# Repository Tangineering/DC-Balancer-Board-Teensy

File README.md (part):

# Scale_Car_Teensy

Teensy 4.1 firmware for a scale FCHEV (Fuel-Cell Hybrid EV) platform — the **Scale Car DC
Balancer Board, Rev 20260622**.

The board is a bidirectional power-pathing balancer: ideal-diode source switches route a fuel
cell and a 2S battery onto a shared VBUS, a regen path returns braking energy to the charger,
and an MPPT module harvests into the battery. This firmware drives that hardware.

It controls:
- motor torque through a VESC (`VescUart` over UART),
- fuel-cell/battery power sharing through dual AD5443 MDAC droop outputs (SPI),
- the RT1987 ideal-diode power-path switches (6 sequenced GPIOs),
- the Silvertel **Ag105** MPPT battery charger (I2C config + `MPPT_DISABLE` GPIO),
- the BQ29200 cell OVP/balancer (`CBAL_DISABLE` GPIO),
- command/telemetry with a Raspberry Pi over UDP Ethernet,
- a safety state machine, Pi watchdog, latching fault handling, and a USB-serial test mode.

> The authoritative hardware sources are `references/Scale Car Teensy IO - IO.csv` (pin map),
> `references/Scale Car Design PCB BOM 20260622.csv` (parts), and the schematic PDF. See
> `CLAUDE.md` for the reconciliation spec and `PLAN.md` for the implementation plan. For
> hardware-in-the-loop testing (a bare Teensy against a simulated plant, no PCB needed), see
> `docs/HIL_MODE.md` (protocol/architecture) and `docs/HIL_USER_MANUAL.md` (operator manual).

## Hardware interfaces

- **UART (`Serial1`)**: VESC motor controller (`RX`=0, `TX`=1).
- **SPI**: two AD5443 MDACs (`CS_MDAC_FC`=36, `CS_MDAC_BT`=37) for FC/BT droop gains; OPA197
  output buffers run from the 5 V rail (hardware bodge).
- **I2C (`Wire`)**: Silvertel **Ag105** charger at address **0x30**.
- **Ethernet/UDP**: command in (port 5001), telemetry out (port 5000), Teensy IP 192.168.1.50.
- **Encoder interrupts**: wheel-speed estimation from `ENC_A`=14 / `ENC_B`=15 (bodged from 2/8 on
  2026-08-16; the optical sensors are hardwired to power, so there is no enable pin).
- **ADC inputs (12-bit)**: FC/BT current (INA253A1, 0.1 V/A), FC/BT/BUS/CHG/RGN voltages.
- **Digital outputs**: FC/BT boost enables, 6 RT1987 path switches, `MPPT_DISABLE`,
  `CBAL_DISABLE`, encoder enable.

### Power-path switches (RT1987 ideal-diode controllers)

| Pin | Name | Role |
|----|------|------|
| 27 | `FC_BUS_ENABLE` | FC regulator → VBUS |
| 28 | `BT_BUS_ENABLE` | BT regulator → VBUS |
| 29 | `MOT_PWR_ENABLE` | VBUS → VESC/motor (Run only) |
| 30 | `REGEN_ENABLE` | regen → charger input |
| 31 | `FC_CHARGE_ENABLE` | VBUS(FC) → charger (guarded) |
| 32 | `BT_SEQUENCE_ENABLE` | battery-pack sequencing (init LOW, then HIGH) |

All switches default LOW at boot (fail-safe; 10 kΩ EN-to-GND bodge resistors back this up).
`FC_CHARGE_ENABLE` and `REGEN_ENABLE` are **mutually exclusive** and are only ever driven
through `assertFcChargeEnable()`, which forces `BT_BUS_ENABLE` and `REGEN_ENABLE` LOW (with an
RT1987 turn-off settle delay) before opening the FC→charger path.

**VBUS bring-up — only enable a boost on a stiff source.** The hazard is *not* bus inrush: VBUS
carries only ~30–40 µF (the RT1987 ceramics); the 470 µF bulk cap is on the V-MOT/regen node behind
`MOT_PWR_ENABLE`. The real failure mode is enabling a boost on a source that can **collapse**:
switching with built-up inductor current on a sagging/recovering rail destroys the power stage. The
exact mechanism is **unconfirmed pending a scope capture** — most likely a VOUT overshoot past the
20 V SW/VOUT abs-max (the TPS61288 OVP is at 19 V, only ~0.5 V of margin, and the 3×22 µF output
caps DC-derate to ~30 µF) and/or transient reverse conduction. Either way the destructive energy
comes from the boost's own inductor/output cap, so *a supply current limit does not bound it*. On a
board-powered Teensy this also motorboats: the boost loads `VBT`, the logic rail browns out, the MCU
resets, and re-enables the boost. So in **production** (`BENCH_TEST=0`, stiff vehicle source) State 0
brings the bus up gently (switches first, then the boosts' own soft-start) and is mirrored by the
State 98 `G` command; the bus is then kept energized through Idle/Finish so a Run never re-hot-plugs
it. Under **`BENCH_TEST`** State 0 keeps the power stage **off** at boot (see State 0 below). Bench
rule: the supply must exceed the logic baseline (≥ ~0.5–1 A) or the board-powered Teensy browns out,
and the bus may be brought up (`G`) only on a stiff supply.

## Runtime flow

Main loop execution order:
1. `updateSensors()`
2. `computeDerivedSignals()`
3. `detectFaults()`
4. `checkPiWatchdog()`
5. `receiveCommands()`
6. state machine (`doState0/1/2/3/98/99`)
7. `pollAg105()` + `sendTelemetry()` at ~50 Hz

## State machine

- **State 0 (Init)**: behavior depends on the `BENCH_TEST` build flag.
  - **Production (`BENCH_TEST=0`)**: a **non-blocking phase machine** that brings VBUS up gently —
    bus switches first (`FC_BUS_ENABLE`/`BT_BUS_ENABLE`), settle, then the FC/BT boosts (their
    soft-start raises the bus; see *VBUS bring-up* above). Raises `BT_SEQUENCE_ENABLE`, inits the
    MDAC and VESC, then **gates the transition to Idle on `V_bus ≥ V_BUS_CHARGED_THRESH`**; if the
    bus never reaches it within `BUS_CHARGE_TIMEOUT_MS`, raises `FAULT_INIT_FAIL` → State 99
    (catches a dead boost, failed switch, or no source).
  - **Bench (`BENCH_TEST=1`, the default flash)**: boots **straight to Idle with the power stage
    OFF** — boosts, bus switches, and `BT_SEQUENCE` all stay LOW, and there is no `V_bus` gate. This
    prevents enabling a boost on a soft/current-limited bench supply (which browns out the
    board-powered Teensy and motorboats the boost to failure). Bring the bus up manually with the
    State 98 `G` command on a stiff supply.
  - Either way the Ag105 is **not** configured here — it is unpowered in Init; `pollAg105()`
    configures it lazily once a charger path powers it. Shared init lives in `initControlPeripherals()`.
- **State 1 (Idle)**: motor current zero, `MOT_PWR_ENABLE` LOW; the bus is left **energized**
  (boosts + bus switches stay ON). Waits for a Run command from the Pi, or `T` on USB serial to
  enter test mode (State 98).
- **State 2 (Run)**: `MOT_PWR_ENABLE` HIGH; run `chargingControl()`, `motorControl()`,
  `powerBalance()`. `chargingControl()` owns the `REGEN`/`FC_CHARGE`/`BT_BUS` switches and the
  `MPPT_DISABLE` line. The bus is already up from Init/Idle, so entering Run does not hot-plug it.
- **State 3 (Finish)**: stops the motor and closes the motor/regen/charge paths, but **leaves the
  boosts + bus switches ON** so the bus stays armed and the next Idle→Run never re-hot-plugs the
  470 µF bus. Clears the wheel-speed buffer and returns to Idle. (No cap/regen drain — the
  disabled-boost back-feed hazard doesn't apply while the boosts stay enabled.)
- **State 98 (Test)**: USB-serial hardware exerciser (see below).
- **State 99 (Error)**: **non-blocking** two-phase safe shutdown that bleeds VBUS/regen energy and
  then disables the boosts and tears the bus down — latched until power cycle (which re-runs the
  State-0 gentle bring-up).

The State 99 shutdown is a phase machine gated on `millis()` (no blocking `delay()`), so
`detectFaults()` keeps sampling through the highest-energy drain windows.

## Charger control (Silvertel Ag105)

There is **no charge-current register to program per-mA**. Control is:
- **I2C config is LAZY, not at init** (`pollAg105()`): the charger is unpowered in
  Init/Idle (no charger power path is open, so it cannot ACK I2C), so reg `0x00 = 0x01`
  (2.5 A profile) and reg `0x01 = 0x08` (2S / 8.4 V) are written the first time
  `chargerHasPower()` is true and the `AG105_SETTLE_MS` bring-up window has elapsed and
  the charger ACKs. Stored in EPROM; the flag re-arms on power loss, so writes are
  idempotent. **fw v24** adds a dynamic reg `0x02` MPPT input-voltage threshold, written
  through the same power-gated lazy path with a read-verify-write handshake and an
  EPROM-wear write-rate budget.
- **`MPPT_DISABLE` GPIO (pin 5, active-LOW)**: LOW inhibits the MPPT loop (during regen,
  so it doesn't fight the fast transient); HIGH releases it (cruise/coast harvest). The
  Ag105's MPPT mechanism is an **input-voltage-threshold regulator** (datasheet p.10),
  not perturb-and-observe — charging commences only once the input exceeds a threshold
  set by reg `0x02` (11–33 V, ~0.088 V/count; default 18 V with no MPPTS resistor
  fitted).
- **I2C polling** (`pollAg105()` at 50 Hz): reads reg `0x06` (measured charge current,
  0.011 A/count) into `I_charge`, and caches the Table-6 status byte. The Ag105 prepends its
  status byte before any read, so each 1-byte field is read as 2 bytes.
- **Readiness** (`ag105IsReady()`): GENSTAT (status bits [2:0]) == Charging (0x02) or
  Fully Charged (0x03).
- An Ag105 I2C read failure only latches State 99 in the charging-relevant states (Run/Finish);
  in Init/Idle/Test a missing or still-powering charger does not lock the system.

## Telemetry & commands

- **Commands**: 22-byte UDP packet (sync `0xBB` + XOR checksum). Fields: timestamp, counter,
  `v_setpoint`, `power_share_setpoint`, `charge_goal`, `mode_cmd`, and a reserved `droop_enable`
  byte (parsed, not yet wired).
- **Telemetry — protocol v4, 58 bytes** (`TELEMETRY_VERSION = 4`, sync `0xAA`, XOR over bytes
  1–56). Carries the measured/derived signals, droop gains, the raw Ag105 Table-6
  `charger_status` byte (offset 51), a `switch_state` bitmask of the 6 path switches, a 16-bit
  `fault_flags`, the latched `error_code`, and `error_source_state`. The Pi bridge parses fixed
  offsets and **must match this version** — see `PLAN.md` §6b for the byte-by-byte layout and the
  block comment above `sendTelemetry()`.

## Key functions

### `motorControl()` + `PI_Controller_Motor()`
Computes torque from speed error (`v_setpoint - v_actual`) and commands VESC current. The
integrator has **anti-windup**: `pi_motor_accum` is clamped to the torque equivalent of
`MOTOR_I_CMD_MAX`. Integrator state is file-scope (resettable by the unit tests).

### `powerBalance()` + `PI_Controller_Power()`
Controls the FC/BT split from measured INA253 currents; PI output (`droopRatio`) is mapped to
FC/BT droop gains and written via `setDroopMdac()` (AD5443, SPI_MODE0, MSB-first, `transfer16`).

### `chargingControl()`
Manages `MPPT_DISABLE` and the regen/FC-charge/BT-bus switches based on `charge_goal`, regen
state (`current < -0.1`), and Ag105 readiness — enforcing the FC-charge/regen mutual exclusion.

### `updateWheelSpeed()` + encoder ISRs
An **edge-period estimator** (fw v12, hardened by the fractional-pitch ledger in fw v15/v17)
measures the period between same-edge-type quadrature transitions to derive flywheel speed →
`v_actual`. It replaced the original boxcar (fixed-window sample-counting) estimator, whose
~113 ms window realized enough group delay to limit-cycle the drive loop at its own crossover.
Direction comes from the quadrature decode; a ring-invalidation event on a direction flip
holds the last valid reading (bounded by a stale timeout) rather than emitting a full-scale
zero step. State 3 resets the estimator between runs so a new run's first samples aren't
measured against stale timestamps.

## Safety features

- FC overcurrent (`I_fc > LIMIT_I_FC_MAX`), BT overcurrent (`I_batt > LIMIT_I_BT_MAX`)
- Battery UV/OV, FC UV — **UV checks are gated to Run (State 2)** so unramped rails at boot
  don't latch State 99
- Bus OV (`LIMIT_V_BUS_MAX = V_BUS_NOMINAL + 1.5 = 17.5 V` at the 16.0 V nominal, below the 19 V TPS61288 HW OVP) and Bus UV (Run only)
- Regen-node and charger-input overvoltage
- Illegal switch combination (`FC_CHARGE_ENABLE` with `BT_BUS`/`REGEN`)
- Ag105 GENSTAT error states (OC/Regulation 0x05, Thermal Shutdown 0x06, Timeout 0x07) and I2C
  comms failure
- Pi watchdog timeout (`PI_TIMEOUT_MS`, States 2/3 only)

Faults funnel through `triggerFault()`, which latches a primary `error_code` + source state and
transitions to **State 99**.

## Fault reference

When any check in `detectFaults()` trips, `triggerFault()` sets that condition's bit in the
16-bit `fault_flags`, latches the **first** cause into `error_code` (and the active state into
`error_source_state`), forces `FAULT_ERROR` (`0x8000`), and transitions to **State 99** —
latched until power cycle. Both `fault_flags` and `error_code` ride in the v4 telemetry packet,
so every value below is observable on the Pi. Read `error_code` for the root cause and
`fault_flags` for everything that tripped.

### Fault flags (`fault_flags` bitmask)

`fault_flags` is an OR of these bits — more than one can be set at once:

| Mask | Flag | Trigger | Limit | Gated to |
|------|------|---------|-------|----------|
| `0x0001` | `FAULT_OC_FC` | `I_fc` overcurrent | `LIMIT_I_FC_MAX = 3.5 A` | all |
| `0x0002` | `FAULT_UV_BATT` | `V_batt` undervoltage | `LIMIT_V_BATT_MIN = 6.2 V` | Run |
| `0x0004` | `FAULT_OV_BUS` | `V_bus` overvoltage | `LIMIT_V_BUS_MAX = 17.5 V` | all |
| `0x0008` | `FAULT_SWITCH_CONFLICT` | `FC_CHARGE_ENABLE` high while `BT_BUS`/`REGEN` high | — | all |
| `0x0010` | `FAULT_PI_TIMEOUT` | Pi watchdog expired | `PI_TIMEOUT_MS` | States 2/3 |
| `0x0020` | `FAULT_OV_BATT` | `V_batt` overvoltage | `LIMIT_V_BATT_MAX = 8.6 V` | all |
| `0x0040` | `FAULT_UV_FC` | `V_fc` undervoltage | `LIMIT_V_FC_MIN = 6.0 V` | Run |
| `0x0080` | `FAULT_OC_BT` | `I_batt` overcurrent | `LIMIT_I_BT_MAX = 6.0 A` | all |
| `0x0100` | `FAULT_UV_BUS` | `V_bus` undervoltage | `LIMIT_V_BUS_MIN = 12.0 V` | Run |
| `0x0200` | `FAULT_OV_RGN` | regen-node overvoltage | `LIMIT_V_RGN_MAX = 28.0 V` | all |
| `0x0400` | `FAULT_OV_CHG` | charger-input overvoltage | `LIMIT_V_CHG_MAX = 24.0 V` | all |
| `0x0800` | `FAULT_I2C_CHARGER` | Ag105 I2C comms failure | — | Run/Finish |
| `0x1000` | `FAULT_CHARGER_STAT` | Ag105 GENSTAT error (`0x05` OC/regulation, `0x06` thermal, `0x07` timeout) | — | charging states |
| `0x2000` | `FAULT_INIT_FAIL` | init failure: VBUS failed to reach `V_BUS_CHARGED_THRESH` within `BUS_CHARGE_TIMEOUT_MS` (also legacy Ag105 config) | `V_BUS_CHARGED_THRESH` | State 0 |
| `0x8000` | `FAULT_ERROR` | latched marker: system entered State 99 | — | set with any fault |

The UV checks marked **"Gated to Run"** are deliberately suppressed outside State 2, so unramped
rails at boot don't latch State 99 (see Safety features above).

### Error codes (`error_code` latched cause)

`error_code` is the single latched primary cause — the *first* fault to fire — and is distinct
from the multi-bit `fault_flags`. `error_source_state` records which state was active when it
latched. Values map 1:1 to `errorCodeStr()`:

| Code | Enum | String |
|------|------|--------|
| `0x00` | `ERR_NONE` | (none) |
| `0x01` | `ERR_OC_FC` | FC overcurrent |
| `0x02` | `ERR_UV_BATT` | Batt undervoltage |
| `0x03` | `ERR_OV_BUS` | Bus overvoltage |
| `0x04` | `ERR_SWITCH_CONFLICT` | Switch conflict |
| `0x05` | `ERR_PI_TIMEOUT` | Pi timeout |
| `0x06` | `ERR_OV_BATT` | Batt overvoltage |
| `0x07` | `ERR_UV_FC` | FC undervoltage |
| `0x08` | `ERR_OC_BT` | BT overcurrent |
| `0x09` | `ERR_UV_BUS` | Bus undervoltage |
| `0x0A` | `ERR_OV_RGN` | Regen overvoltage |
| `0x0B` | `ERR_OV_CHG` | Charger input OV |
| `0x0C` | `ERR_I2C_CHARGER` | Ag105 I2C fail |
| `0x0D` | `ERR_CHARGER_STAT` | Ag105 STAT fault |
| `0x0E` | `ERR_INIT_FAIL` | Init failure |

**Recovery:** State 99 is latched — a fault clears only on a power cycle. Diagnose with
`error_code` (root cause) first, then inspect the full `fault_flags` bitmask for any secondary
conditions that tripped in the same tick.

## Test mode (State 98)

State 98 is a USB-serial hardware exerciser for bench bring-up. **Enter** it by sending `T`
while in Idle (State 1); **exit** with `Q`, which returns to Idle and forces `MOT_PWR_ENABLE`
LOW. The Pi watchdog is suspended in this state, but `detectFaults()` still runs every tick — a
fault latches State 99 exactly as in normal operation. `FC_CHARGE_ENABLE` only ever moves through
`assertFcChargeEnable()`, even here.

### Serial command set

All commands are single characters over USB serial; every toggle echoes the resulting pin state
back over serial:

| Key | Action | Notes |
|-----|--------|-------|
| `F` | Toggle `FC_REG_ENABLE` (FC boost) | |
| `B` | Toggle `BT_REG_ENABLE` (BT boost) | |
| `1` | Toggle `FC_BUS_ENABLE` | **ON refused** if FC boost is ON and `V_bus` < `V_BUS_CHARGED_THRESH` (hot-plug guard — use `G`) |
| `2` | Toggle `BT_BUS_ENABLE` | same hot-plug guard as `1`; **also refused** while `FC_CHARGE_ENABLE` is HIGH (illegal combination) |
| `3` | Toggle `MOT_PWR_ENABLE` | ON allowed **only at a regulated bus** (`motPwrConnectBlocked()`); must be HIGH before `D`/`R` |
| `4` | Toggle `REGEN_ENABLE` | forces `FC_CHARGE` off via `assertFcChargeEnable(false)` before going HIGH |
| `5` | Toggle `FC_CHARGE_ENABLE` | always through the `assertFcChargeEnable()` guard |
| `6` | Toggle `BT_SEQUENCE_ENABLE` | |
| `C` | Toggle `CBAL_DISABLE` | HIGH = OVP bypassed (prints a warning) |
| `M` | Toggle `MPPT_DISABLE` | HIGH = MPPT harvesting; LOW = inhibited |
| `N` | Dynamic Ag105 MPPT reg-`0x02` threshold status/verify (fw v24) | read-verify-write handshake against the EPROM-wear write-rate budget; see `CLAUDE.md`'s 2026-09-01a addendum |
| `G` | Staged bus bring-up | `busBringupTick()` phases P0–P3: bus alone → boosts → dwell → motor node; `X` aborts (stage dark) |
| `D` | Start/stop simulated drive cycle | requires `MOT_PWR_ENABLE` HIGH and the calibrated velocity chain |
| `S` | Print status dump (all pins, ADCs, `I_charge`, faults, bench-tool state) | read-only |
| `I` | Scan the I2C bus | read-only |
| `E` | One-shot VESC firmware + telemetry read | blocks up to ~100 ms (bench-only) |
| `U` | Toggle VESC watch (~2 Hz `[VW]` line, flags fault changes) | **rebound from `W` (2026-08-10)**; auto-paused during profiles and plot mode |
| `P` | Set power-share setpoint (prompts for a value) | closed-loop: `powerBalance()` drives the MDACs live; needs current flowing |
| `O` | Set droop ratio 0.15–0.85 (prompts for a value) | open-loop direct MDAC write; no current needed — the calibration entry point |
| `A` | Set manual motor current in A (prompts) | constant VESC current, bypasses the drive controller |
| `V` | Set manual motor velocity in m/s (prompts) | refused until the velocity chain is calibrated |
| `R` | Start/stop power-share profile sweep | needs `A`/`V` set + `MOT_PWR_ENABLE` HIGH; stop parks switches |
| `T <Imax> <hold s> <rate A/s>` | Start trapezoidal current profile (one line, e.g. `T 6 5 0.5`) | direct phase-current ramp; `T` alone while running stops it; switches left as-is |
| `Y [Vmax] [b]` | Start combined drive-cycle + power-share profile (one line, both args optional, e.g. `Y 1 0.3`) | sweeps velocity **and** share together; same prerequisites as `D`; `Y` alone while running stops it |
| `W [Imax] [b]` | Start combined **current** + power-share profile (one line, both args optional, e.g. `W 6 0.0`) | same table as `Y` with the motor axis in amps; no encoder needed; `W` alone while running stops it |
| `X` | Universal stop | cancels any profile/bring-up/armed run + manual motor + live share loop |
| `L` | Toggle Serial-Plotter stream | 50 Hz `sp,act,gFC,gBT,ifc,ibt` line; suppresses status lines; `R`/`T` arm with a 5 s delay |
| `K` | Print SD-card logging status | card present, current/last file, record/drop counts; read-only |
| `H` / `?` | Print the command list | |
| `Q` | Exit → Idle (State 1) | forces `MOT_PWR_ENABLE` LOW, closes charge/regen paths, drops plot mode |

### Serial-Plotter stream (`L`)

For live plotting in the Arduino IDE (Tools → Serial Plotter). `L` toggles a condensed 50 Hz
line — `sp:…,act:…,gFC:…,gBT:…,ifc:…,ibt:…` (share setpoint, measured share, both droop gains,
both channel currents; all naturally 0–3 so the plotter's shared autoscale keeps every trace
readable). While ON, the periodic human-readable output that would break the plotter's parser is
suppressed: the `[PS]`/`[DC]`/`[TP]` 500 ms snapshots, phase banners, and the `[VW]` watch line
(VESC faults latch, so they're still reported once plotting stops). Because the IDE 2.x plotter
has no send box, `R` and `T` under plot mode **arm** the run and fire it 5 s later — switch to
the plotter window during the countdown. The arm cancels on the same key again, `X`, `Q`,
turning `L` off, or any other run starting; `R`'s preconditions are re-checked at fire time.
Arming is refused while another profile is already running, and arming the other profile
supersedes a pending arm with an explicit cancel message.

### SD-card logging (`K` / automatic)

Logs the power-share/motor/bus signals at the full 1 kHz control cadence to the Teensy's
built-in micro-SD — 20x finer than the 50 Hz `L` stream, needed to see the Youla-H share loop's
actual transient. Logging starts and stops automatically with the profile lifecycle: it opens
when `R`, `T`, `D`, `Y`, or `W` starts, and closes on natural completion, the matching stop-toggle, `X`,
`Q`, or a fault (the close is deferred out of the fault transition and held until the State-99
teardown is latched, so it cannot lengthen a teardown dwell). There's no separate arm command — a card present at profile start is logged, a missing
one is silently skipped. No card in the slot, a full card, or a write error never faults the
board or blocks a profile: the firmware prints a warning and keeps running. `K` prints a
status line — card present, current/last file name (`PS`/`TP`/`DC`/`YP`/`WP` prefix by profile type),
record and drop counts — and stays live
even during the bring-up lockout. It reports no free-space figure on purpose: the FAT-walking
calls that would produce one block for seconds on a real card. Retrieve a run by pulling the card (`PSnnnn.BLG` /
`TPnnnn.BLG` / `DCnnnn.BLG` / `YPnnnn.BLG` / `WPnnnn.BLG` in the root) and decode it on the laptop:

```
python tools/decode_benchlog.py FILE.BLG > run.csv
```

### Combined drive-cycle + power-share profile (`Y`)

`D` moves the velocity with the share held still; `R` moves the share with the motor held still.
`Y` moves **both at once**, which is the only way to see the cross-coupling the vehicle actually
runs in — the velocity loop's changing bus draw against the share loop's changing droop split.
It's a fixed 40 s, 16-region table: solo ramps and steps on each axis (so you can still fit a
per-axis response from the same run), two deliberately simultaneous regions (a combined ramp and a
combined step), buffers between excitations to let each transient settle, and two brief excursions
to the share extremes (all-FC, all-BT) to check the droop clamp.

Both arguments are optional and go on one line with the key:

```
Y 1 0.3
```

- **`Vmax`** (m/s, default `1.0`) scales the table's normalised velocity waypoints, so the same
  profile works at any bench speed. Must be greater than 0 and no more than 5.0 m/s — the same
  ceiling the `V` manual-velocity key enforces.
- **`b`** (default `0`) clips the share setpoint to `[b, 1−b]`, for keeping a fragile setup away
  from the share extremes. Must satisfy `0 ≤ b < 0.5` (at 0.5 the band collapses to a point and
  the share axis flattens, so it's refused). Above 0.35 it still runs but prints a warning: the
  clip then starts eating the table's intermediate plateaus, not just the 0/1 bound checks.

The clip is applied *after* interpolation, so a ramp that crosses the bound keeps its normal slope
and then flattens — that kink is deliberate, not a bug. A bare `Y` + Enter runs the defaults.

Like `R` and `T` — and unlike `D` — `Y` does **not** run the charging manager. That's deliberate:
`chargingControl()` would open the FC charge path mid-run, which drops the battery off the bus and
pins the measured share at 1.0, destroying the very thing the run is measuring. Your charge and
regen switches stay exactly where you set them, so a share experiment behaves as though
`charge_goal` were 0 no matter what the Pi last commanded; coast-down regen is soaked up by the
hardware braking chopper as always. `Y` also starts immediately under plot mode rather than
arming like `R`/`T` (its prerequisites are checked at the keypress, which an arming delay would
undermine); a pending `R`/`T` arm is refused over, and cancelled by, a running `Y`.

Prerequisites are the same as `D`: no bring-up in progress, a calibrated velocity chain, and
`MOT_PWR_ENABLE` HIGH (key `3`). Press `Y` again to stop — the motor is zeroed and the path
switches parked, exactly as stopping `D` or `R` does. On natural completion the motor is zeroed
and the share returns to 0.50, with the switches left as they are (matching how `D`/`R` finish).
`X` and `Q` stop it like any other profile — and note that **stopping parks all the switches, so
the bus is dark and you need another `G` before the next run** (a natural completion doesn't).
Runs log automatically to `YPnnnn.BLG` (same
`decode_benchlog.py`, no format change — the profile's region index appears in *both* the
drive-cycle and power-share phase columns, which is how you recognize a combined run).

### Combined current + power-share profile (`W`)

`Y` needs a calibrated encoder chain, which the bench doesn't have yet — so `W` is the combined-axis
run you can actually do today. It's the same 16-region, 40 s table, with the motor axis
reinterpreted as **commanded current** instead of velocity. Everything about the motor side follows
`T`: current goes straight to the VESC, the velocity PI is never involved, no calibration is
required, and `MOT_PWR_ENABLE` LOW is only a warning (your VESC may have its own supply).

```
W 6 0.0
```

- **`Imax`** (A, default `5.0`) scales the table's normalised motor column — at the default the
  plateaus are 0 / 3.0 / 5.0 / 2.5 / 1.0 A. Must be greater than 0 and no more than 25 A, the same
  ESC ceiling `T` uses; peaks above the 5 A budget are allowed, exactly as in `T`. Negative peaks
  are refused here (the table already coasts back to zero — use `T` for a braking ramp).
- **`b`** works exactly as in `Y`, with the same clip, the same bounds, and the same warning above
  0.35.

Stopping (`W` again) zeroes the motor, returns the share to 0.50, and parks the path switches —
the `Y`/`R` convention rather than `T`'s, because this profile sweeps the share and therefore owns
the source configuration during the run. **A stopped run leaves the bus dark, so you need a fresh
`G` bring-up before the next one** (a run that finishes on its own leaves the switches alone). `X` and `Q` stop it like any other profile, and it's
mutually exclusive with `D`, `R`, `T`, and `Y`. Runs log to `WPnnnn.BLG`; the region index lands in
the power-share and trapezoid phase columns (`Y` uses power-share and drive-cycle), which is how
you tell the two combined runs apart in a decoded CSV.

**Note the key change:** `W` used to be the VESC watch. That moved to **`U`** ("UART watch").
Pressing `W` never starts anything by itself — it opens a parameter prompt you can cancel — so old
muscle memory can't launch a motor profile by accident.

**Watch out: the share extremes now open a bus switch** (this applies to `Y` as well as `W`). Regions 6 and 11 push the share all the
way to one source, and since the full-span change that no longer just clips the droop — the starved
channel is physically taken off the bus (its RT1987 switch opens while the motor is drawing). If
your bound `b` is below 0.15 the run will do this twice, and both profiles print a warning at start
saying so. Do the first such run scope-armed and at low current (`W 2 0.2`). Two things follow when
you read the log: while a channel is off the bus the share loop is open (no MDAC writes at all), so
the R6/R11 samples are topology events rather than controller response — don't fit a plant through
them. And if a run *finishes* with a channel still cut off, the firmware puts it back on the bus
automatically; if it can't (bus not in regulation) it says so, and `X`, `Q`, or the next `G` clears
it.

### Testing an individual component

1. Connect a USB-serial terminal and send `T` to enter test mode from Idle.
2. Send `S` to capture a baseline snapshot of all pin states and ADC readings.
3. Toggle the line(s) you want to exercise with the keys above; the firmware echoes each new
   state so you can confirm the write landed.
4. Re-send `S` to read back the effect on the relevant ADC/pin.
5. Send `Q` to exit (this forces `MOT_PWR_ENABLE` LOW).

Mind the guarded keys: `5` (`FC_CHARGE_ENABLE`) always runs through `assertFcChargeEnable()`,
which drives `BT_BUS_ENABLE`/`REGEN_ENABLE` LOW first; `4` (`REGEN_ENABLE`) forces `FC_CHARGE`
off before going HIGH; `1`/`2` refuse to connect a source to the bus while the matching boost is
running and the bus is discharged (use `G` to energize the bus safely first); and `C`
(`CBAL_DISABLE` HIGH) bypasses cell OVP — use with care.

### Running the emulated drive cycle

1. Set `MOT_PWR_ENABLE` HIGH first with key `3` — `D` aborts with an error otherwise.
2. Press `D` to start. While active, `advanceDriveCycle()` supplies a pre-programmed
   `v_setpoint`, and the real `chargingControl()` / `motorControl()` / `powerBalance()` run
   unmodified, in the same call order as State 2 — only the setpoint source differs.
3. A `[DC]` status line prints every 500 ms: `t`, `v_sp`, `v_act`, `V_bus`, `I_fc`, `I_bt`,
   `I_chg`, and `FLT` (fault flags). (Suppressed while the `L` plot stream is on.)
4. Press `D` again to stop early — the firmware flushes a zero VESC command and parks all path
   switches via `safeAllSwitches()`.

The profile runs through these phases (from `DRIVE_CYCLE[]`):

| Phase | Duration | `v_setpoint` | Purpose |
|-------|----------|--------------|---------|
| 0 Standstill | 2 s | 0.0 | verify sensors, confirm no faults |
| 1 Ramp-up | 4 s | 0.0 → 3.0 | linear ramp; `motorControl()` live |
| 2 Cruise | 6 s | 3.0 | steady speed; `powerBalance()` live |
| 3 Coast-down | 3 s | 3.0 → 0.0 | linear ramp down |
| 4 Regen hold | 3 s | −0.5 | negative setpoint (regen braking) |
| 5 Standstill | 2 s | 0.0 | confirm `I_charge > 0` if charging |

On completion `v_setpoint` returns to 0, but `MOT_PWR_ENABLE` is left as the operator set it —
toggle it off with `3`, or exit with `Q` (which forces it LOW).

## Unit tests

A host-native suite in `test/` builds and runs with `g++` — no Teensy or Arduino IDE required:

```bash
cd test && make           # or: g++ -std=c++17 -Wall -Wextra -I. -I.. test_main.cpp -o run_tests
```

Mocks stub the Teensy/Arduino, Wire, SPI, VESC, and Ethernet APIs. Coverage includes scale-factor
math, fault detection (incl. GENSTAT decode and UV boot-gating), the Youla-H drive controller's
Hanus-conditioned recursion (replay-vector-verified) and its PI fallback's convergence +
anti-windup, command parsing, telemetry packing (58-byte v4 layout + checksum), the Ag105
init/poll I2C sequences, `assertFcChargeEnable()` ordering, `pollAg105()` state gating,
`doState0()` init-fault handling, the State 98 drive cycle, and the edge-period velocity
estimator (incl. the fractional-pitch ledger and TOCTOU reset fix). It also covers the SD-card
bench logger: lifecycle on every profile exit path (complete/stop/`X`/`Q`/fault), the 1 kHz
rate gate, ring-buffer overflow drop-and-count, no-card and mid-run write-error tolerance, file
naming/collision, the BLG v7 (106-byte) record schema, and `K` status output. The `Y` and `W`
combined profiles (parameter parsing/clip/region walk/exit paths/`YP`+`WP` logging/suppression)
are covered too.

There are **three build targets**: `-DBENCH_TEST=0` (production), `-DBENCH_TEST=1` (bench), and
the HIL build (`-DHIL_SIM=1 -DUSE_ETHERNET=1`). The test Makefile needs
`-I../controller_design_MIMO` for the drive-controller replay vectors. Run all before every
flash.

`tools/decode_benchlog.py` has its own stdlib-only self-test, `tools/test_decode_benchlog.py`
(no pytest/g++ needed): it generates synthetic `.BLG` files and asserts on the decoder's actual
output — a wrap-straddling run decodes in full, a brownout tail is truncated at the true end,
`close_reason` 6 (`io_error`) decodes correctly, and gap statistics (`max_interval_us`,
`missed_periods`) come out right for a known gap. Run with:

```bash
python tools/test_decode_benchlog.py
```

The Python tooling (HIL simulator/suite, EMS tools, analysis) has its own pytest suites under
`tools/`: stdlib-only ones run under `.venv_hil` (`.venv_hil\Scripts\python.exe -m pytest tools/
--ignore=tools/test_figures.py`), numpy-side ones under miniforge — see `docs/HIL_USER_MANUAL.md`
§3.2.5 and the latest CLAUDE.md addendum for the current counts.

## Notes for calibration

Items marked `TODO(calibrate)` / `TODO(verify)` in the source still need bench values, including:
- `SCALE_V_CHG` / `SCALE_V_RGN` dividers, and confirmation of the FC/BT/BUS dividers
- the Youla-H drive controller's coefficients are GENERATED (`drive_controller_coeffs.h`) and
  must never be hand-edited; `MOTOR_I_CMD_MAX` (anti-windup bound) is `constexpr`-pinned against
  them via `static_assert`. `motorConstant` is **dead on the shipped build**
  (`USE_YOULA_DRIVE_CONTROLLER` default 1 sends the controller's amps straight through
  `commandMotorCurrent()`) — the PI + `motorConstant` path survives only as the `=0` fallback.
- the VBUS bring-up tunables: `V_BUS_CHARGED_THRESH`, `BUS_SETTLE_MS`, `BUS_CHARGE_TIMEOUT_MS`
- the regen-detection threshold and the State 99 cap-drain / regen-decay delays
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
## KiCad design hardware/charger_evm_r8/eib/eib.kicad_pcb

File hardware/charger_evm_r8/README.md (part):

# Charger EVM r9: design review guide

## 1. Purpose and how to read this document

This README presents the r9 charger design for operator review, with progressive detail. Section 2 shows the overall
functional block diagram and the architecture. Section 3 lists what changed on 2026-11-12; a reader who needs only the
changes can read section 3 alone. Sections 4 to 7 explain the design concepts, the permit gate, the operating modes and the
firmware consequences. Sections 8 to 12 cover the physical implementation, status, plan, open items and the source
index. Appendix A defines the abbreviations and the identifier families.

The full record is the design document `docs/charger_bq25798_wiring_design_2026-11-05.md` (revision r9). Section 12 maps
each topic to its authoritative file and section. Neither text that the design document marks "superseded", "withdrawn"
or "history" nor the r7-outline work in `archive_r7_outline/` is the current design.

**State after phases A and B (2026-11-14; the 2026-11-15 paragraph below adds phase C).** (**Superseded 2026-11-15:** "Current state (2026-11-14).") The read-only review `REVIEW_2026-11-14.md` and the five simulations of `sim/`
(overview in `sim/README.md`) were answered in the 2026-11-14 round. `LAYOUT_DECISIONS.md` section 1 gives the board
status, and D-70 to D-84 record the changes. Copper is unchanged on both boards. The silkscreen carries pin-1 marks,
wire-pad maps, lead labels and board markings; the EIB stencil has no apertures on DNP pads; the netlist carries the
ordered parts. The ordering set is `bom_2026-11-14/`. The fab packages `fab/cr_2026-11-14/` and `fab/eib_2026-11-14/`
were written on 2026-11-15 by `gen/export.sh cr 2026-11-14` and `gen/export.sh eib 2026-11-14`. (**Superseded
2026-11-14, packages exported:** "are to be written by `gen/export.sh cr 2026-11-14` and `gen/export.sh eib
2026-11-14`; the last exported packages are `fab/cr_2026-11-13f/` and `fab/eib_2026-11-13c/`.") Section 11 lists the operator questions of the round. Where this
README and section E of the design document disagree with `bom_2026-11-14/` on a part, quantity or MPN, the BOM
governs (REVIEW DOC-1). Design revision r9-25 reconciled section E with `bom_2026-11-14/`, and r9-26 corrected its
residual rows (**Superseded 2026-11-15, REVIEW R2-DOC-1:** "section E has not been revised for the 2026-11-13 order
rulings"). Those rulings set one
BQ25798EVM, no spare U101, 6 CR and 3 EIB boards, and a J-TAP mate from workshop stock (design-document change rows
r9-21 and r9-22; `LAYOUT_DECISIONS.md` section 1). D-66 replaced the W5 ribbon and the J101/J201 headers by nine
soldered wires between two 3 x 3 wire-pad grids, so the CR no longer lifts off without desoldering (section 8.5).

**Current state (2026-11-15, phase C).** A second review of the r9-25 records (findings R2-*) was answered in phase C
of the same round. `update_2026-11-14/notes_phaseC_*.md` hold the per-finding status and the evidence, and
`LAYOUT_DECISIONS.md` D-85 to D-92 record the changes. The board edits are silkscreen texts only: "VIN1" and "GND"
labels at the CR input pair W1/W2 (D-85) and an F.Silkscreen number beside every EIB E pad (D-86). The netlist
carries corrected or new Note fields (D-88), and the BOM set holds five opt-in SPARE lines (D-89). Both packages were
written again in place on 2026-11-15 (D-90). Copper is unchanged on both boards. The design document is at revision
r9-30 (2026-11-16) (**Superseded 2026-11-16, r9-30:** "r9-29"; **superseded 2026-11-16, r9-29:** "r9-28"; **superseded 2026-11-16, r9-28:** "r9-27"), and the companion document is at revision r5 (**Superseded 2026-11-16, r9-30:** "r4"). Design r9-30 records the operator rulings of 2026-11-16 on the charger I2C and the FC window: 100 kHz with the existing 10 kOhm MB pull-ups (PM9 withdrawn), an FR-07 budget of 3.5 ms from the pin-34 rising edge to REG03-05 write complete (was 1.5 ms), FC-window close at G < 0.40 A and admission at G >= 0.50 A (was 0.30 A); D-96 records them. A regen-image VINDPM of 18.4 V was evaluated the same day and deferred by the operator ("Let's keep at 19V for now then, with a note to revisit later if necessary."), so the regen image stays at VINDPM 19.0 V (design J.2 item 91). Table 11.4
lists the operator questions; the J.2 item 84
spare-U101 question affects the Mouser order, and the SPARE lines affect the Digi-Key order. The J.2 item 74 ruling
(2026-11-15, D-93) accepts the charger dropout on hard brakes and leaves the Mouser order unchanged. The rulings of
2026-11-16 close J.2 item 83 by a D-36 exemption for /CHG_ARM with a build check (D-94). They keep the EIB reference
rule set and the CR W6 "GND" label as they are (D-95). Neither ruling changes copper or a package. A third ruling of
2026-11-16 keeps the W5 grid copper and adopts the staged T-A-06 metering as the single-bridge mitigation (D-80
ruling; design r9-29). (**Superseded 2026-11-16, D-80 ruling:** "The W5 grid question stays open; D-80 carries a
2026-11-16 addendum with new findings.")

## 2. Architecture

### 2.1 Block diagram

Three different parts carry the refdes J1. In this document, **CR J1** is the 22-pin CHG header (TSW strips). **MB
J1/J2** are the Teensy 4.1 Dubox receptacles, and **EVM J1** is the charger VIN screw terminal.

Figure 2.1 shows the power and signal architecture of the charger path. Power flows from VBUS or V-MOT into the EVM and
returns to the pack through CR J1 pads 18/19.

Figure 2.1. Charger path, block diagram (r9).

The diagram is schematic and not to scale. Thick red conductors carry power and thin blue lines carry logic or analog
signals; a bridge marks a crossing with no connection. The source is `gen/readme_figures.py`. Figures 2.1 and 5.1 were regenerated on 2026-11-15 for the fitted
hardware: U101 TCKE1401NM, nine W5 wires, the J-TAP mate from workshop stock and R131B/R132 at 4.99 kOhm (REVIEW
R2-DOC-6; `LAYOUT_DECISIONS.md` D-92). Only CR J1 pad 11 and the J-TAP conductors enter the permit gate. Table 2.2, section 8.6 and
design-document sections A.5 and C give the EIB-to-EVM leads and the EVM modifications.

### 2.2 Blocks

Table 2.1 lists each block, its role and its physical location.

Table 2.1. Blocks of the charger path.

| Block | Role | Physical location |
|---|---|---|
| MB RT1987 switches D-BC-FC, D-BC-RG | Route VBUS (FC charging) or V-MOT (regen) into VCHG-IN | MB, existing parts |
| MB D-BT-SQ (RT1987) | Connects the charger output net VCHG to the pack VBT | MB, existing part |
| CR J1 (22-pin CHG header) | Mates the CR to the 22 former Ag105 holes | CR underside, TSW strips in MB SSQ sockets |
| eFuse U101 TCKE1401NM (D-67; superseded: TPS26630RGER) | Input current limit 2.37 A typical (about 1.97-2.77 A, D-67); UVLO rising 9.86 V and OVP rising 23.19 V typical; with pin leakage UVLO rising 9.055-10.548 V and OVP rising 21.588-25.019 V (`sim/efuse_decay/RESULTS.md` Table 1); fault output (FLAG) and IMON | CR top |
| Permit gate | Four comparators and five LVC packages; holds the converter off unless a release term is true | CR top |
| J-TAP (J102) | Brings the ten tap conductors onto the CR | CR, THT header, +x side |
| EVM (BQ25798) | Buck-boost charger, I2C address 0x6B | Off-board, on an insulating plate fixed to the chassis |
| EIB | Converts CR logic levels into /CE, ILIM_HIZ hold/release and the FC current clamp at the EVM | 2-layer board on two M3 x 10 mm nylon standoffs on the EVM plate |
| Teensy 4.1 | Commands CHG_ARM, CHG_QUAL and the RT1987 enables; reads readbacks and I2C | MB, on J1/J2 receptacles |

Every block in Table 2.1 appears in Figure 2.1. Only the MB switches, the eFuse and the EVM carry charger power; the
other blocks carry logic.

### 2.3 Interfaces

Table 2.2 lists each interface, its connector and what crosses it.

Table 2.2. Interfaces of the charger path.

| Interface | Connector | What crosses it |
|---|---|---|
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
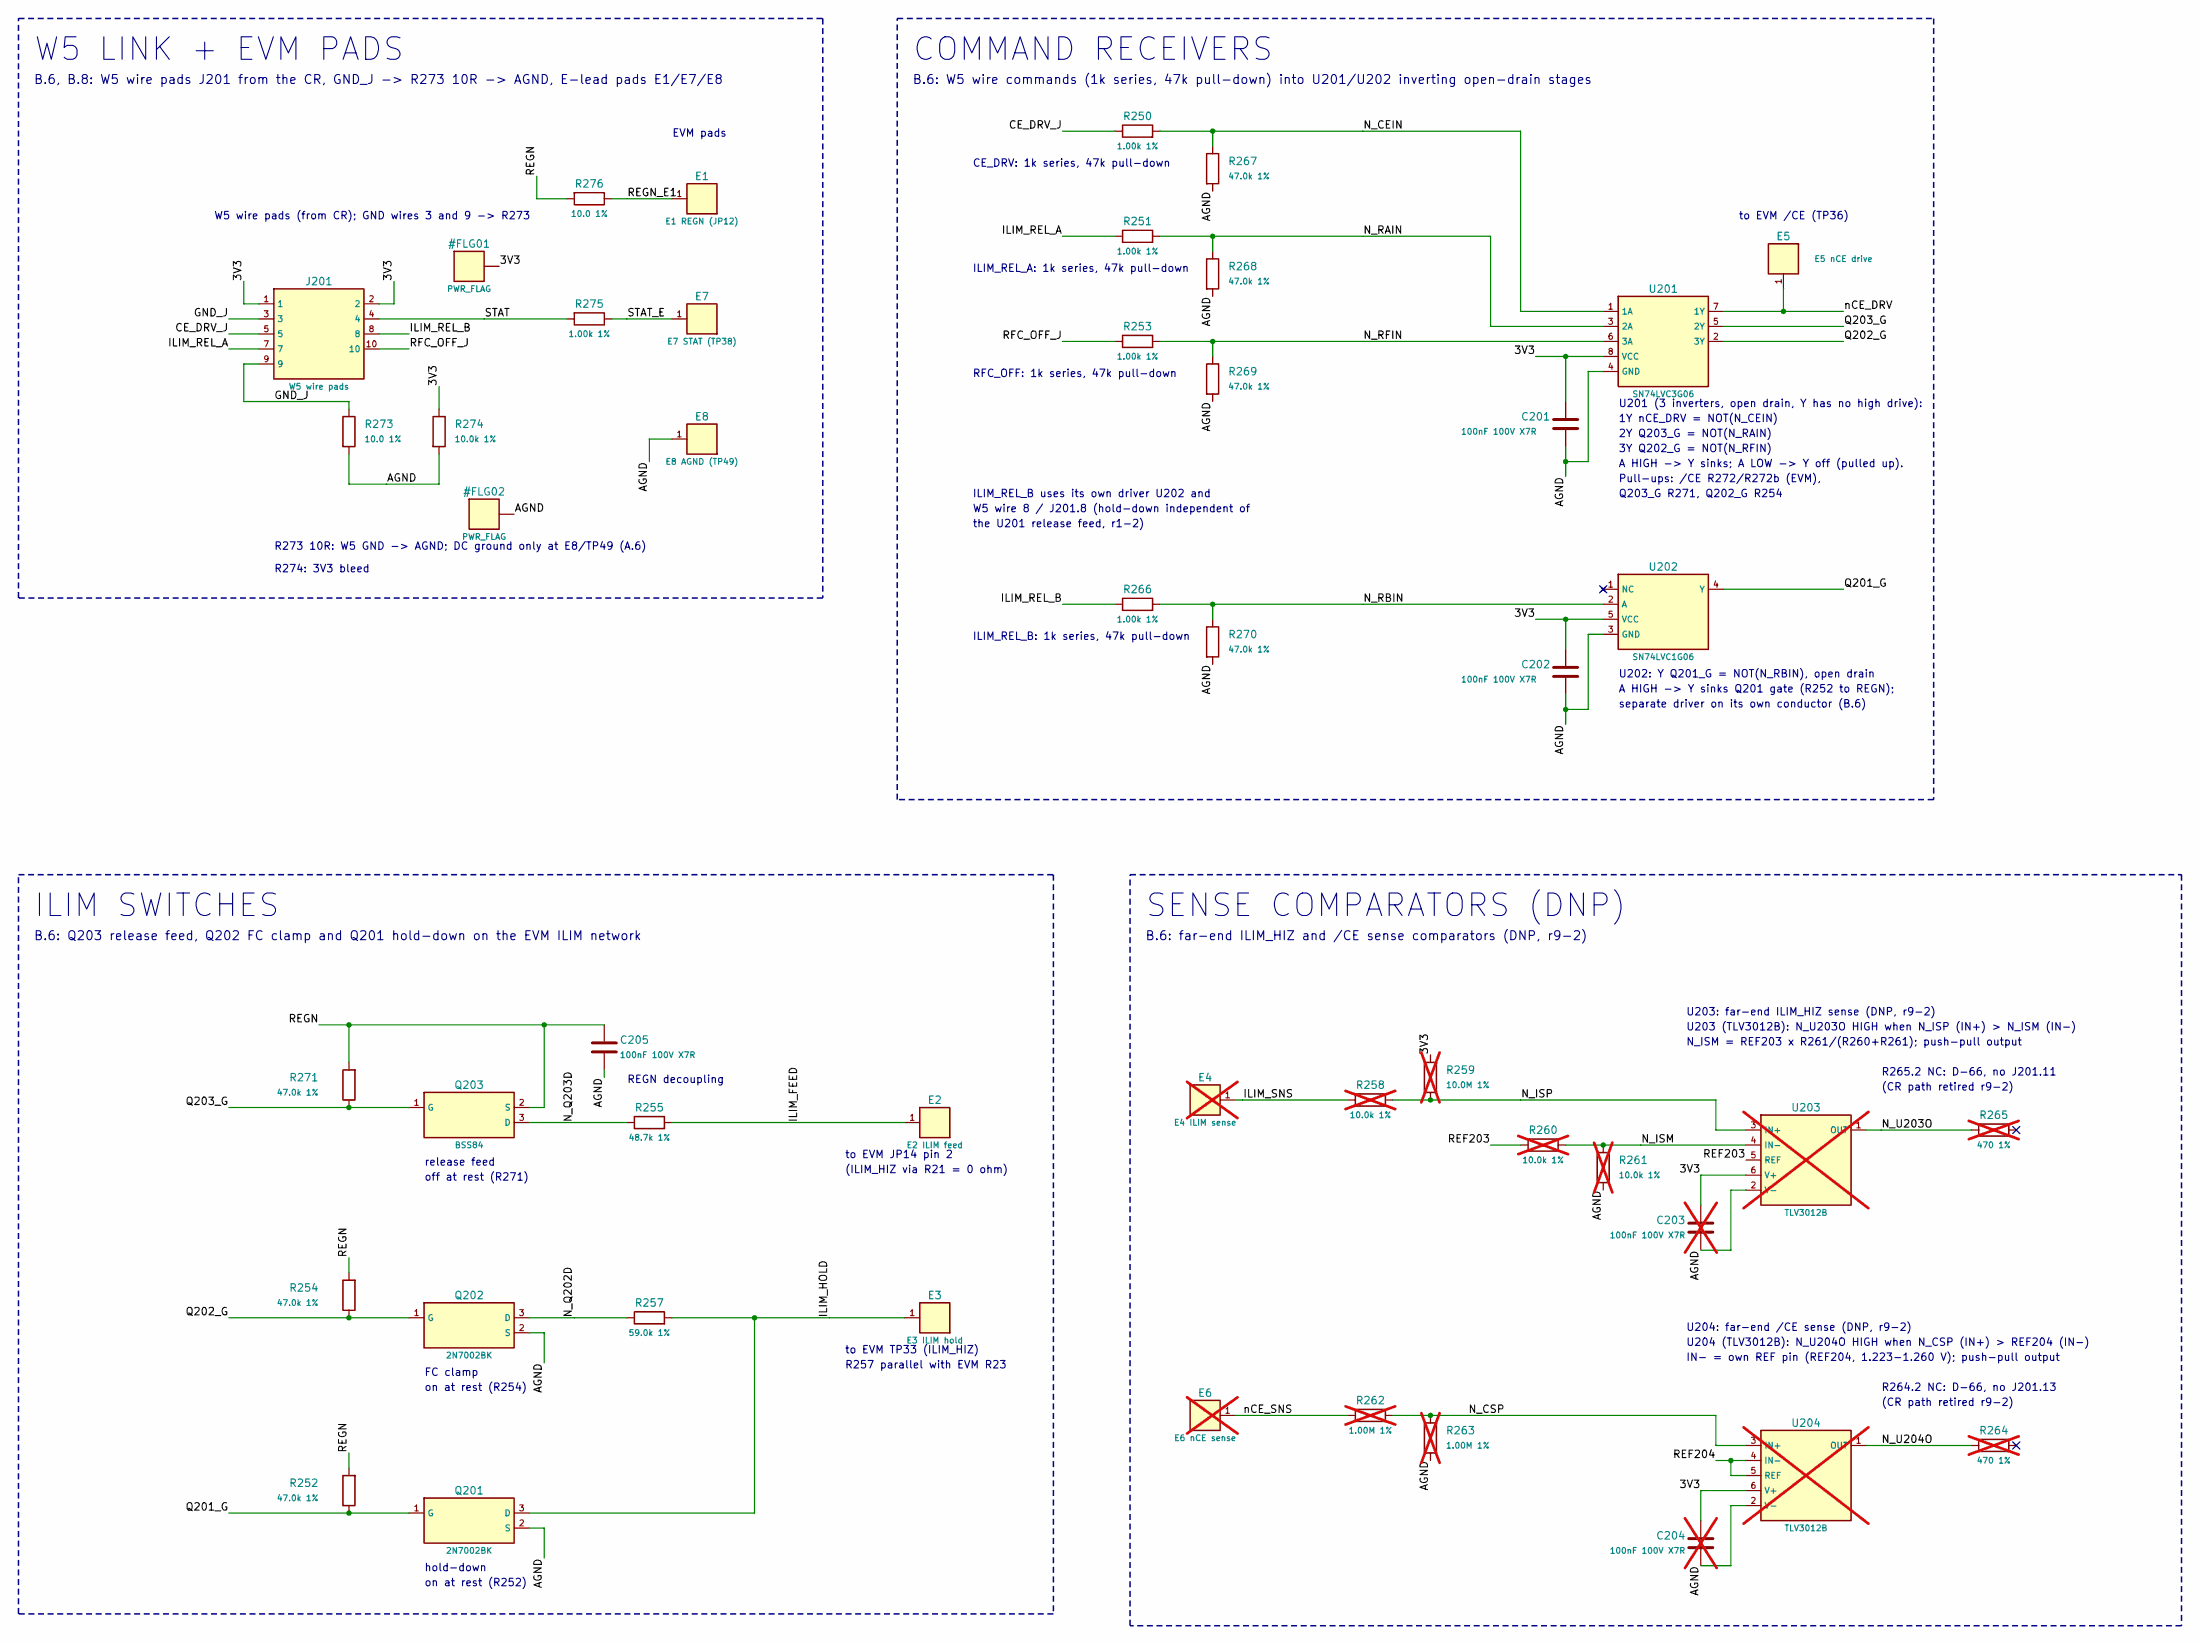
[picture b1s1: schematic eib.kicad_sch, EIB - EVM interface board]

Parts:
C201, C202, C205: 100nF 100V X7R; C_0603_1608Metric_CrtYd0.10; MPN GRM188R72A104KA35D
C203, C204: 100nF 100V X7R; C_0603_1608Metric_CrtYd0.10; MPN GRM188R72A104KA35D; not fitted
E1: E1 REGN (JP12); LeadPad_PTH_D1.0mm_P1.8mm
E2: E2 ILIM feed; LeadPad_PTH_D1.0mm_P1.8mm
E3: E3 ILIM hold; LeadPad_PTH_D1.0mm_P1.8mm
E4: E4 ILIM sense; LeadPad_PTH_D1.0mm_P1.8mm; not fitted
E5: E5 nCE drive; LeadPad_PTH_D1.0mm_P1.8mm
E6: E6 nCE sense; LeadPad_PTH_D1.0mm_P1.8mm; not fitted
E7: E7 STAT (TP38); LeadPad_PTH_D1.0mm_P1.8mm
E8: E8 AGND (TP49); LeadPad_PTH_D1.0mm_P1.8mm
J201: W5 wire pads; WirePads_PTH_3x3_D1.0mm_Pad1.8mm_P2.54mm_CrtYd0.10
Q201, Q202: 2N7002BK; SOT-23_CrtYd0.10; MPN 2N7002BK,215
Q203: BSS84; SOT-23_CrtYd0.10; MPN BSS84LT1G
R250, R251, R253, R266, R275: 1.00k 1%; R_0603_1608Metric_CrtYd0.10; MPN CRCW06031K00FKEA
R252, R254, R267, R268, R269, R270, R271: 47.0k 1%; R_0603_1608Metric_CrtYd0.10; MPN CRCW060347K0FKEA
R255: 48.7k 1%; R_0603_1608Metric_CrtYd0.10; MPN CRCW060348K7FKEA
R257: 59.0k 1%; R_0603_1608Metric_CrtYd0.10; MPN CRCW060359K0FKEA
R258, R260, R261: 10.0k 1%; R_0603_1608Metric_CrtYd0.10; MPN CRCW060310K0FKEA; not fitted
R259: 10.0M 1%; R_0603_1608Metric_CrtYd0.10; MPN CRCW060310M0FKEA; not fitted
R262, R263: 1.00M 1%; R_0603_1608Metric_CrtYd0.10; MPN CRCW06031M00FKEA; not fitted
R264, R265: 470 1%; R_0603_1608Metric_CrtYd0.10; MPN CRCW0603470RFKEA; not fitted
R273, R276: 10.0 1%; R_0603_1608Metric_CrtYd0.10; MPN CRCW060310R0FKEA
R274: 10.0k 1%; R_0603_1608Metric_CrtYd0.10; MPN CRCW060310K0FKEA
U201: SN74LVC3G06; Texas_DCT0008A_SSOP-8_TI-land_CrtYd0.10; MPN SN74LVC3G06DCTR
U202: SN74LVC1G06; Texas_DCK-5_SC-70-5_CrtYd0.10; MPN SN74LVC1G06DCKT
U203, U204: TLV3012B; SOT-23-6_CrtYd0.10; MPN TLV3012BIDBVR; not fitted

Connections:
/3V3: C201.1, C202.1, C203.1, C204.1, J201.1, J201.2, R259.2, R274.1, U201.8 (VCC), U202.5 (VCC), U203.6 (V+), U204.6 (V+)
/AGND: C201.2, C202.2, C203.2, C204.2, C205.2, E8.1, Q201.2 (S), Q202.2 (S), R261.2, R263.2, R267.2, R268.2, R269.2, R270.2, R273.2, R274.2, U201.4 (GND), U202.3 (GND), U203.2 (V-), U204.2 (V-)
/CE_DRV_J: J201.5, R250.1
/GND_J: J201.3, J201.9, R273.1
/ILIM_FEED: E2.1, R255.2
/ILIM_HOLD: E3.1, Q201.3 (D), R257.2
/ILIM_REL_A: J201.7, R251.1
/ILIM_REL_B: J201.8, R266.1
/ILIM_SNS: E4.1, R258.1
/N_CEIN: R250.2, R267.1, U201.1 (1A)
/N_CSP: R262.2, R263.1, U204.3 (IN+)
/N_ISM: R260.2, R261.1, U203.4 (IN-)
/N_ISP: R258.2, R259.1, U203.3 (IN+)
/N_Q202D: Q202.3 (D), R257.1
/N_Q203D: Q203.3 (D), R255.1
/N_RAIN: R251.2, R268.1, U201.3 (2A)
/N_RBIN: R266.2, R270.1, U202.2 (A)
/N_RFIN: R253.2, R269.1, U201.6 (3A)
/N_U203O: R265.1, U203.1 (OUT)
/N_U204O: R264.1, U204.1 (OUT)
/Q201_G: Q201.1 (G), R252.1, U202.4 (Y)
/Q202_G: Q202.1 (G), R254.1, U201.2 (3Y)
/Q203_G: Q203.1 (G), R271.1, U201.5 (2Y)
/REF203: R260.1, U203.5 (REF)
/REF204: U204.4 (IN-), U204.5 (REF)
/REGN: C205.1, Q203.2 (S), R252.2, R254.2, R271.2, R276.2
/REGN_E1: E1.1, R276.1
/RFC_OFF_J: J201.10, R253.1
/STAT: J201.4, R275.2
/STAT_E: E7.1, R275.1
/nCE_DRV: E5.1, U201.7 (1Y)
/nCE_SNS: E6.1, R262.1

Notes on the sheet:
W5 LINK + EVM PADS
B.6, B.8: W5 wire pads J201 from the CR, GND_J -> R273 10R -> AGND, E-lead pads E1/E7/E8
W5 wire pads (from CR); GND wires 3 and 9 -> R273
EVM pads
R273 10R: W5 GND -> AGND; DC ground only at E8/TP49 (A.6)
R274: 3V3 bleed
COMMAND RECEIVERS
B.6: W5 wire commands (1k series, 47k pull-down) into U201/U202 inverting open-drain stages
CE_DRV: 1k series, 47k pull-down
ILIM_REL_A: 1k series, 47k pull-down
RFC_OFF: 1k series, 47k pull-down
ILIM_REL_B: 1k series, 47k pull-down
ILIM_REL_B uses its own driver U202 and
W5 wire 8 / J201.8 (hold-down independent of
the U201 release feed, r1-2)
to EVM /CE (TP36)
U201 (3 inverters, open drain, Y has no high drive):
1Y nCE_DRV = NOT(N_CEIN)
2Y Q203_G = NOT(N_RAIN)
3Y Q202_G = NOT(N_RFIN)
A HIGH -> Y sinks; A LOW -> Y off (pulled up).
Pull-ups: /CE R272/R272b (EVM),
Q203_G R271, Q202_G R254
U202: Y Q201_G = NOT(N_RBIN), open drain
A HIGH -> Y sinks Q201 gate (R252 to REGN);
separate driver on its own conductor (B.6)
ILIM SWITCHES
B.6: Q203 release feed, Q202 FC clamp and Q201 hold-down on the EVM ILIM network
release feed
off at rest (R271)
FC clamp
on at rest (R254)
hold-down
on at rest (R252)
REGN decoupling
to EVM JP14 pin 2
(ILIM_HIZ via R21 = 0 ohm)
to EVM TP33 (ILIM_HIZ)
R257 parallel with EVM R23
SENSE COMPARATORS (DNP)

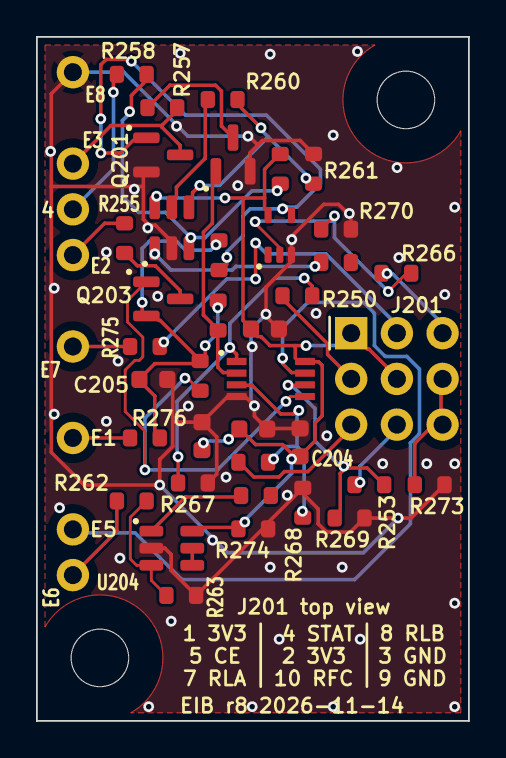
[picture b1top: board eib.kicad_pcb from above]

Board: 2 copper layers, 24.0 x 38.0 mm, 48 parts (0 on the bottom side), 32 nets.

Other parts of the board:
H1, H2: MountingHole_3.2mm_M3_KeepOut7mm

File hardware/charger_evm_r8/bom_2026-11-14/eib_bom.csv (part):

Internal SKU,Part,PCB Names,Specification,Category,Manufacturer,Mft. SKU,Vendor,Vendor SKU,Link,Datasheet,BOM Qty,BOM Units,Cost / BOM Unit,Assembly Cost,Pricing Status,MOQ (for price),Ready to Order,Ordered,Received,Board Operating Current [mA],Voltage Min [V],Voltage Max [V],Series Min Voltage [V],Series Max Voltage [V],Max Current [mA],Max Power [W],Board Power [W],Max Pulse Current [mA],Max Operating Temp [C],Max Junction Temp [C],Junction - SP Resistance [C/W],Naive Junction Temp Rise [C],Max Other Resistance [C/W],Notes,Total Assembly Cost:,$0.00,,PCB components:,25,PCB unique parts:,11
,"Capacitor, MLCC","C201,C202,C205",100 nF 100 V X7R 0603,CR/EIB capacitor,Murata Electronics,GRM188R72A104KA35D,Digikey,490-3285-1-ND,https://www.digikey.com/en/products/result?keywords=GRM188R7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,,3,ea,,,not verified,,FALSE,FALSE,FALSE,,,100,,,,,,,,,,,,"Replaced 2026-11-13 (Digi-Key upload review): Murata GRM188R71H104KA93D (50 V) is obsolete (Digi-Key 2026-11-13); GRM188R72A104KA35D is Digi-Key's 'upgrade' substitute (100 V, same series and case). Per-unit qty = 3 (one EIB). Voltage rating from the Digi-Key description 'CAP CER 0.1UF 100V X7R 0603' (upload result 2026-11-13b). Digi-Key part number, stock and price from the upload result of 2026-11-13 (bom_2026-11-13/digikey_upload_result_2026-11-13b.csv).",,,,,,,
,N-MOSFET 60 V logic level,"Q201,Q202","60 V N-MOSFET, SOT-23, Vgs(th) max 2.1 V",EIB discrete,Nexperia USA Inc.,"2N7002BK,215",Digikey,1727-4789-1-ND,"https://www.digikey.com/en/products/result?keywords=2N7002BK,215",,2,ea,,,not verified,,FALSE,FALSE,FALSE,,,60,,,,,,,,,,,,"Replaced 2026-11-13 (Digi-Key upload review): onsemi 2N7002KT1G has 0 stock at Digi-Key with no restock date (2026-11-13); Nexperia 2N7002BK,215 has the same SOT-23 pinout and a lower maximum threshold (2.1 V against 2.3 V). The Q201 and Q202 gates are pulled to REGN (4.8-5.2 V at VBUS 15 V, SLUSDV2C p.15) through R252 and R254 47.0 kOhm and sunk by the open-drain U202 and U201 (gen/netlist.py), not driven from 3.3 V. 2N7002BK Vgs(th) max TODO(verify: Nexperia 2N7002BK datasheet). Diodes 2N7002K-7 was not taken (Vgs(th) max 2.5 V). (Superseded 2026-11-14, BOM-9: ""which suits the 3.3 V gate drive of Q201 and Q202"".) Per-unit qty = 2 (one EIB). Digi-Key part number, stock and price from the upload result of 2026-11-13 (bom_2026-11-13/digikey_upload_result_2026-11-13b.csv).",,,,,,,
,P-MOSFET 50 V,Q203,"50 V, 130 mA, SOT-23, |VGS(th)| <= 2.0 V required",EIB discrete,onsemi,BSS84LT1G,Digikey,BSS84LT1GOSCT-ND,https://www.digikey.com/en/products/result?keywords=BSS84LT1G,https://www.onsemi.com/pdf/datasheet/bss84lt1-d.pdf,1,ea,,,not verified,,FALSE,FALSE,FALSE,,,50,,,,,,,,,,,,"Per-unit qty = 1 (one EIB). Index notes BSS84LT1 (without G) is obsolete: order the G part. VGS(th) max <= 2.0 V TODO(verify: onsemi datasheet), T-A-05. Digi-Key part number, stock and price from the upload result of 2026-11-13 (bom_2026-11-13/digikey_upload_result_2026-11-13b.csv).",,,,,,,
,Resistor,"R250,R251,R253,R266,R275",1.00 kOhm 1 % 100 ppm/K 0603 thick film,CR/EIB resistor,Vishay Dale,CRCW06031K00FKEA,Digikey,541-1.00KHCT-ND,https://www.digikey.com/en/products/result?keywords=CRCW0603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,https://www.vishay.com/docs/20035/dcrcwe3.pdf,5,ea,,,not verified,,FALSE,FALSE,FALSE,,,,,,,,,,,,,,,"Per-unit qty = 5 (one EIB). Vishay D/CRCW e3 doc 20035 (rev 14-Apr-2026): 1 %/100 ppm range 10 Ohm to 10 MOhm. Digi-Key part number, stock and price from the upload result of 2026-11-13 (bom_2026-11-13/digikey_upload_result_2026-11-13b.csv).",,,,,,,
,Resistor,"R252,R254,R267,R268,R269,R270,R271",47.0 kOhm 1 % 100 ppm/K 0603 thick film,CR/EIB resistor + EVM rework,Vishay Dale,CRCW060347K0FKEA,Digikey,541-47.0KHCT-ND,https://www.digikey.com/en/products/result?keywords=CRCW0603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,https://www.vishay.com/docs/20035/dcrcwe3.pdf,7,ea,,,not verified,,FALSE,FALSE,FALSE,,,,,,,,,,,,,,,"Per-unit qty = 7 (one EIB). Vishay D/CRCW e3 doc 20035 (rev 14-Apr-2026): 1 %/100 ppm range 10 Ohm to 10 MOhm. 9 on CR/EIB plus EVM R272 and R272b (EM2). Digi-Key part number, stock and price from the upload result of 2026-11-13 (bom_2026-11-13/digikey_upload_result_2026-11-13b.csv).",,,,,,,
,Resistor,R255,48.7 kOhm 1 % 100 ppm/K 0603 thick film,EIB resistor,Vishay Dale,CRCW060348K7FKEA,Digikey,541-48.7KHCT-ND,https://www.digikey.com/en/products/result?keywords=CRCW0603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,https://www.vishay.com/docs/20035/dcrcwe3.pdf,1,ea,,,not verified,,FALSE,FALSE,FALSE,,,,,,,,,,,,,,,"Per-unit qty = 1 (one EIB). Vishay D/CRCW e3 doc 20035 (rev 14-Apr-2026): 1 %/100 ppm range 10 Ohm to 10 MOhm. Digi-Key part number, stock and price from the upload result of 2026-11-13 (bom_2026-11-13/digikey_upload_result_2026-11-13b.csv).",,,,,,,
,Resistor,R257,59.0 kOhm 1 % 100 ppm/K 0603 thick film,EIB resistor,Vishay Dale,CRCW060359K0FKEA,Digikey,541-59.0KHCT-ND,https://www.digikey.com/en/products/result?keywords=CRCW0603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,https://www.vishay.com/docs/20035/dcrcwe3.pdf,1,ea,,,not verified,,FALSE,FALSE,FALSE,,,,,,,,,,,,,,,"Per-unit qty = 1 (one EIB). Vishay D/CRCW e3 doc 20035 (rev 14-Apr-2026): 1 %/100 ppm range 10 Ohm to 10 MOhm. Digi-Key part number, stock and price from the upload result of 2026-11-13 (bom_2026-11-13/digikey_upload_result_2026-11-13b.csv).",,,,,,,
,Resistor,"R273,R276",10.0 Ohm 1 % 100 ppm/K 0603 thick film,EIB resistor,Vishay Dale,CRCW060310R0FKEA,Digikey,541-10.0HCT-ND,https://www.digikey.com/en/products/result?keywords=CRCW0603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,https://www.vishay.com/docs/20035/dcrcwe3.pdf,2,ea,,,not verified,,FALSE,FALSE,FALSE,,,,,,,,,,,,,,,"Per-unit qty = 2 (one EIB). Vishay D/CRCW e3 doc 20035 (rev 14-Apr-2026): 1 %/100 ppm range 10 Ohm to 10 MOhm. Spare is the R276 spare of section E. 10 Ohm is the bottom of the 1 %/100 ppm range (inside). Digi-Key part number, stock and price from the upload result of 2026-11-13 (bom_2026-11-13/digikey_upload_result_2026-11-13b.csv).",,,,,,,
,Resistor,R274,10.0 kOhm 1 % 100 ppm/K 0603 thick film,CR/EIB resistor,Vishay Dale,CRCW060310K0FKEA,Digikey,541-10.0KHCT-ND,https://www.digikey.com/en/products/result?keywords=CRCW0603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,https://www.vishay.com/docs/20035/dcrcwe3.pdf,1,ea,,,not verified,,FALSE,FALSE,FALSE,,,,,,,,,,,,,,,"Per-unit qty = 1 (one EIB). Vishay D/CRCW e3 doc 20035 (rev 14-Apr-2026): 1 %/100 ppm range 10 Ohm to 10 MOhm. Digi-Key part number, stock and price from the upload result of 2026-11-13 (bom_2026-11-13/digikey_upload_result_2026-11-13b.csv).",,,,,,,
,Triple open-drain inverter,U201,"SN74LVC3G06, SSOP-8 (DCT)",EIB IC,Texas Instruments,SN74LVC3G06DCTR,Digikey,296-13280-1-ND,https://www.digikey.com/en/products/result?keywords=SN74LVC3G06DCTR,https://www.ti.com/lit/ds/symlink/sn74lvc3g06.pdf,1,ea,,,not verified,,FALSE,FALSE,FALSE,,,,,,,,,,,,,,,"Per-unit qty = 1 (one EIB). Digi-Key part number, stock and price from the upload result of 2026-11-13 (bom_2026-11-13/digikey_upload_result_2026-11-13b.csv).",,,,,,,
,Single open-drain inverter,U202,"SN74LVC1G06, SC70-5 (DCK)",EIB IC,Texas Instruments,SN74LVC1G06DCKT,Digikey,296-32290-1-ND,https://www.digikey.com/en/products/result?keywords=SN74LVC1G06DCKT,,1,ea,,,not verified,,FALSE,FALSE,FALSE,,,,,,,,,,,,,,,"Replaced 2026-11-13 (Digi-Key upload review): SN74LVC1G06DCKR had 2 pieces in stock at Digi-Key (2026-11-13); SN74LVC1G06DCKT is the same part on a 250-piece reel (1,237 in stock). Per-unit qty = 1 (one EIB). Digi-Key part number, stock and price from the upload result of 2026-11-13 (bom_2026-11-13/digikey_upload_result_2026-11-13b.csv).",,,,,,,
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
